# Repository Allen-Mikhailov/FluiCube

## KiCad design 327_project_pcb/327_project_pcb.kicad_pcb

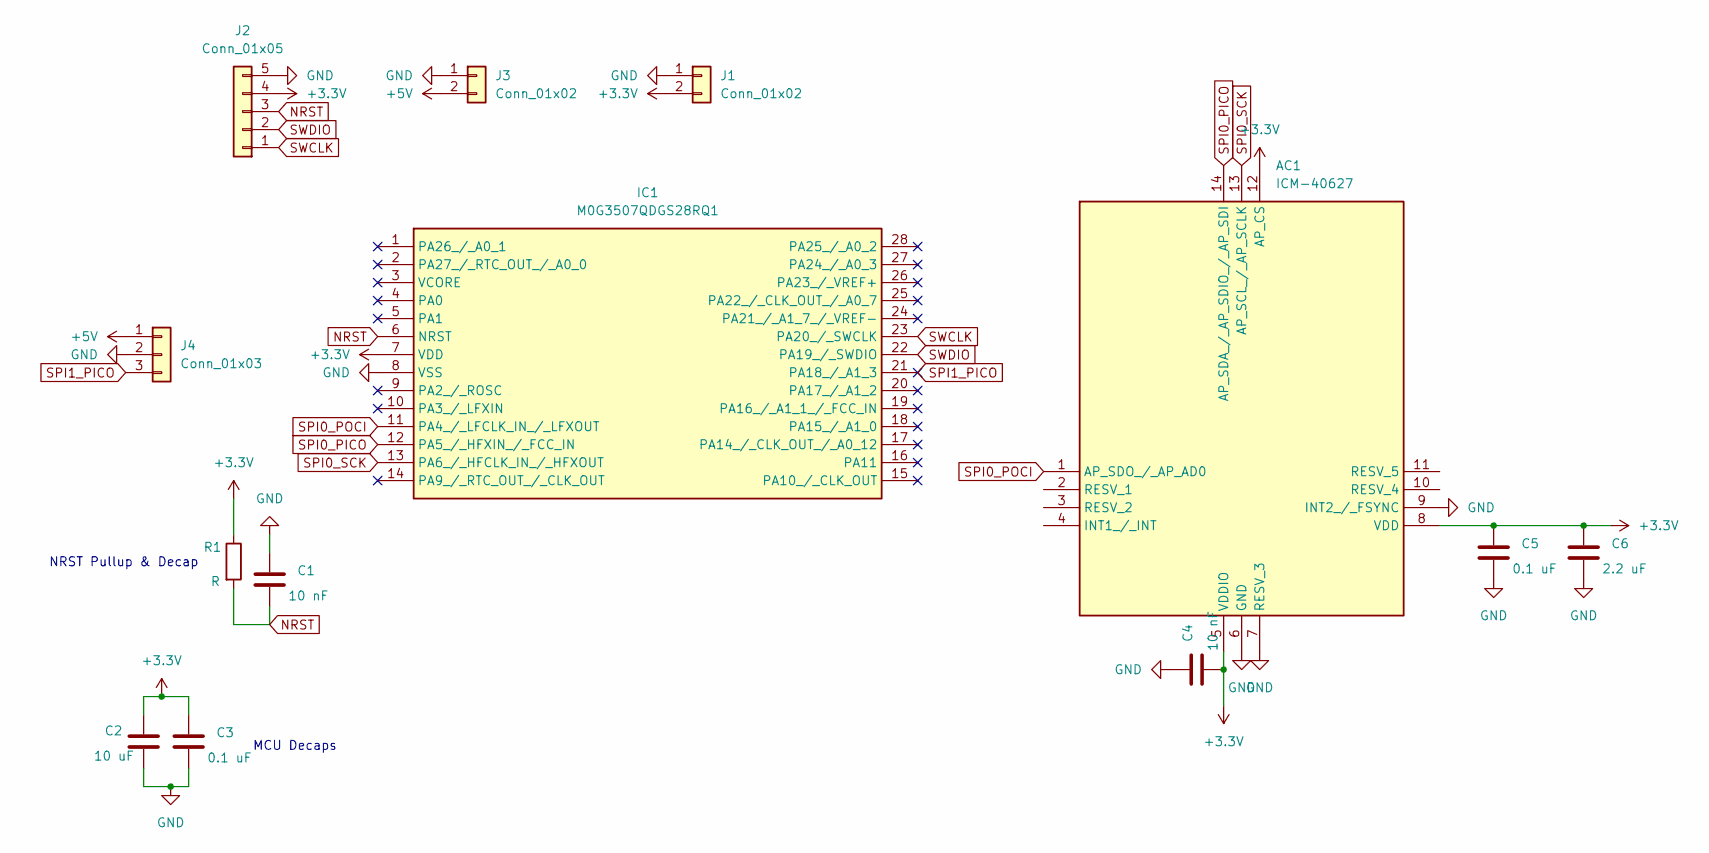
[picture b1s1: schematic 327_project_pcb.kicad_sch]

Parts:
AC1: ICM-40627; IIM42352; Manufacturer_Part_Number ICM-40627; Mouser Part Number 410-ICM-40627
C1: 10 nF; C_0805_2012Metric_Pad1.18x1.45mm_HandSolder
C2: 10 uF; C_1210_3225Metric_Pad1.33x2.70mm_HandSolder
C3: 0.1 uF; C_0805_2012Metric_Pad1.18x1.45mm_HandSolder
C4: 10 nF; CP_Radial_D5.0mm_P2.50mm
C5: 0.1 uF; CP_Radial_D4.0mm_P2.00mm
C6: 2.2 uF; CP_Radial_D4.0mm_P2.00mm
IC1: M0G3507QDGS28RQ1; SOP50P490X110-28N; Manufacturer_Part_Number M0G3507QDGS28RQ1; Mouser Part Number 595-M0G3507QDGS28RQ1
J1, J3: Conn_01x02; PinHeader_1x02_P2.54mm_Vertical
J2: Conn_01x05; PinHeader_1x05_P2.54mm_Horizontal
J4: Conn_01x03; PinHeader_1x03_P2.54mm_Vertical
R1: R; R_0805_2012Metric_Pad1.20x1.40mm_HandSolder

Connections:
+3.3V: AC1.5 (VDDIO), AC1.8 (VDD), AC1.12 (AP_CS), C2.1, C3.1, C4.2, C5.1, C6.1, IC1.7 (VDD), J1.2, J2.4, R1.1
+5V: J3.2, J4.1
GND: AC1.6 (GND), AC1.7 (RESV_3), AC1.9 (INT2_/_FSYNC), C1.1, C2.2, C3.2, C4.1, C5.2, C6.2, IC1.8 (VSS), J1.1, J2.5, J3.1, J4.2
NRST: C1.2, IC1.6 (NRST), J2.3, R1.2
SPI0_PICO: AC1.14 (AP_SDA_/_AP_SDIO_/_AP_SDI), IC1.12 (PA5_/_HFXIN_/_FCC_IN)
SPI0_POCI: AC1.1 (AP_SDO_/_AP_AD0), IC1.11 (PA4_/_LFCLK_IN_/_LFXOUT)
SPI0_SCK: AC1.13 (AP_SCL_/_AP_SCLK), IC1.13 (PA6_/_HFCLK_IN_/_HFXOUT)
SPI1_PICO: IC1.21 (PA18_/_A1_3), J4.3
SWCLK: IC1.23 (PA20_/_SWCLK), J2.1
SWDIO: IC1.22 (PA19_/_SWDIO), J2.2

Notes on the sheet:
NRST Pullup & Decap
MCU Decaps

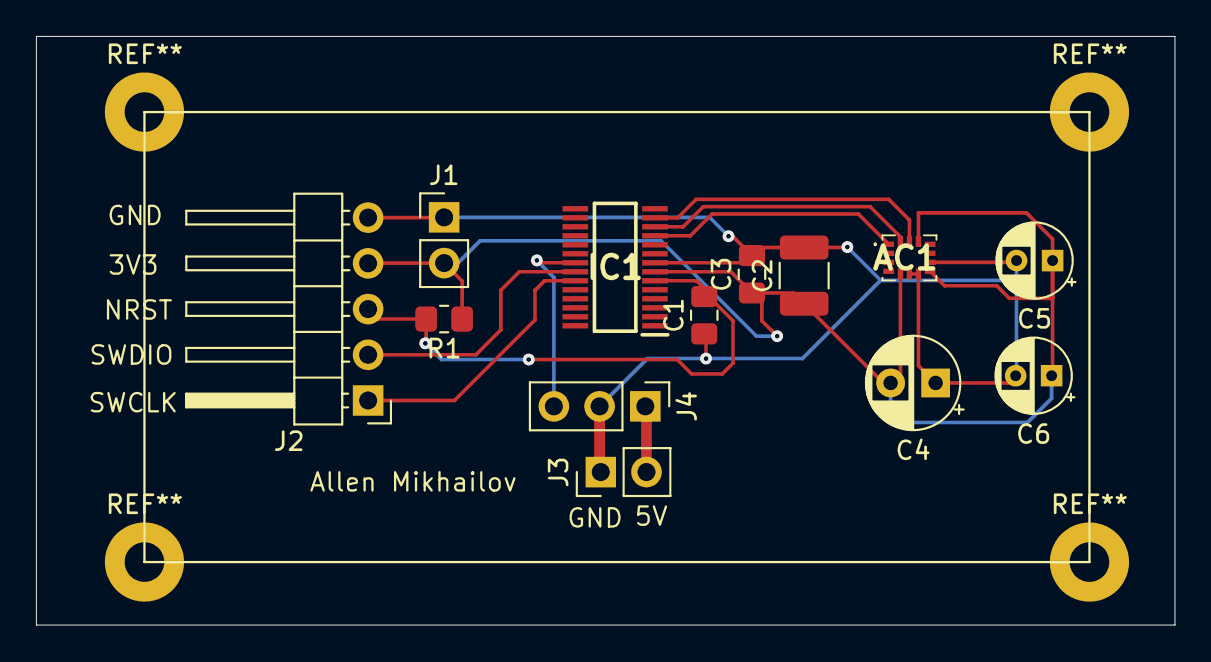
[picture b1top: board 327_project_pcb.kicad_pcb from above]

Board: 2 copper layers, 63.2 x 32.7 mm, 13 parts (0 on the bottom side), 10 nets.

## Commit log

2025-05-08 Inital Transfer from private elec 327 repo
2025-05-08 Added extra files
2025-05-08 Major changes to the website
2025-05-08 Project comments
2025-05-20 Attempt to add all 3 colors. Will have to check if compiles on windows
2025-05-20 Made it rainbow, and got it to work on the cube
2025-07-23 Fixed some issues with the code around orientation and startup, also reverted back to just blue
